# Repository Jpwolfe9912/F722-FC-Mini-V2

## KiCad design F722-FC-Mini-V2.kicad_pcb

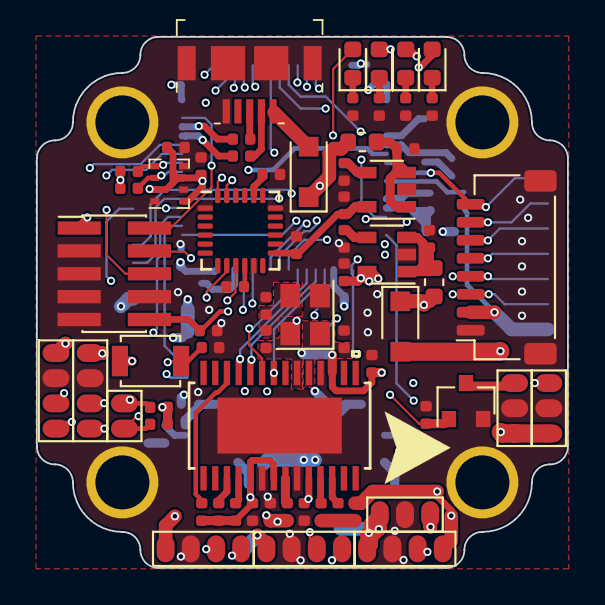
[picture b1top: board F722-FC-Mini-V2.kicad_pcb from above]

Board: 6 copper layers, 29.5 x 29.5 mm, 112 parts (0 on the bottom side), 91 nets.

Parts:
C1, C13, C17: 1uF; C_0402_1005Metric
C2, C14, C18: 10nF; C_0402_1005Metric
C3: 4.7uF; C_0402_1005Metric
C4, C5, C6, C7, C8, C9, C10, C15, C21, C22, C24, C25, C27, C31, C33, C45, C47: 0.1uF; C_0402_1005Metric
C11, C16, C19, C46: 2.2uF; C_0402_1005Metric
C12, C20: 10uF; C_0402_1005Metric
C23, C26: 22uF; C_0603_1608Metric
C28, C29: 10pF; C_0402_1005Metric
C30, C32: 4.7uF; C_0603_1608Metric
C34, C35: 820pF; C_0402_1005Metric
D1, D2, D4, D6: 90V, 2A; D_SOD-123F
D3: RED; LED_0603_1608Metric
D5: BLUE; LED_0603_1608Metric
D7: YELLOW; LED_0603_1608Metric
D9: GREEN; LED_0603_1608Metric
FB1, FB3: 100 @ 100 Mhz; L_0603_1608Metric
FB2: 100 @ 100 MHz; L_0603_1608Metric
H1, H2, H3, H4: MountingHole_Pad; MountingHole_3mm_M2_20x20
J1, J4, J6: Conn_01x03; Conn_3Pin
J2, J3, J7, J11, J13: Conn_01x04; Conn_4Pin
J5: Conn_01x06; JST_SH_SM06B-SRSS-TB_1x06-1MP_P1.00mm_Horizontal
J9: Conn_01x08; JST_SH_SM08B-SRSS-TB_1x08-1MP_P1.00mm_Horizontal
J10: Conn_01x08; Conn_FC_Solder_8
J12: Conn_01x02; Conn_2Pin
J14: UJ2-MIBH-4-SMT-TR; USB_Micro_B_Female_UJ2-MIBH-G-SMT-TR
J16: Conn_02x05_Odd_Even; PinHeader_2x05_P1.27mm_Vertical_SMD
L1, L2: 15uH; L_Bourns-SRN3015
L5: Arrow
Q1: BSS138; SOT-23
R1, R9, R10, R12, R21, R23, R31: 1k; R_0402_1005Metric
R2, R18, R27: 10k; R_0402_1005Metric
R3, R4: 3.7k; R_0402_1005Metric
R5, R8: 4.7k; R_0402_1005Metric
R6: 330; R_0402_1005Metric
R7, R15: 22; R_0402_1005Metric
R11, R20: 20k; R_0402_1005Metric
R13, R22: 3.8k; R_0402_1005Metric
R14, R16: 75; R_0402_1005Metric
R17: 589; R_0402_1005Metric
R19, R25: 200k; R_0402_1005Metric
R24, R28: 56k; R_0402_1005Metric
R26: 100; R_0402_1005Metric
SW1: SW_Push; SW_SPST_B3U-1000P
U1, U3: LP2985-3.3; SOT-23-5
U2: STM32F722RETx; LQFP-64_10x10mm_P0.5mm
U4: BMP280; Bosch_LGA-8_2x2.5mm_P0.65mm_ClockwisePinNumbering
U5, U8: MP4462; DFN-10-1EP_3x3mm_P0.5mm_EP1.7x2.5mm
U6: MAX7456EUI+; MAX7456EUI&plus_T
U7: MPU-6000; InvenSense_QFN-24_4x4mm_P0.5mm
U10: W25Q128JVS; SOIC-8_5.23x5.23mm_P1.27mm
Y1: 27MHz; Oscillator_SMD_Abracon_ASE-4Pin_3.2x2.5mm
Y2: CSTNE8M00G55Z000R0; OSC_CSTNE8M00G55Z000R0

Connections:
+3.3VA: C13.1, C14.1, FB2.1, U2.13
+3V3: C3.1, C4.1, C5.1, C6.1, C8.1, C9.1, C10.1, C16.1, C24.1, C25.1, C27.1, D3.2, FB2.2, J16.1, R1.1, R3.1, R4.1, R5.2, R8.2, R10.1, R12.1, SW1.1, U1.5, U2.1, U2.19, U2.32, U2.48, U2.64, U4.2, U4.6, U4.8, U6.3, U6.19, U6.21, U6.24, U10.3, U10.7, U10.8
+3V3_GYRO: C19.1, C45.1, U3.5, U7.13
+4V5: D1.1, D2.1, FB1.2, FB3.2, J3.1
+5V: C23.1, D1.2, D7.2, J1.1, J2.1, J6.1, J7.1, J13.1, L2.2, R11.1
+5V_USB: D2.2, J14.1
+9V: C26.1, J4.1, J5.1, J11.1, L1.2, R20.1
/Barometer/I2C3_SCL: R5.1, U2.41, U4.4
/Barometer/I2C3_SDA: R8.1, U2.40, U4.3
/CAM: C22.1, J4.3, R16.2
/Connectors/BUZ-: J1.3, Q1.3
/Connectors/CURR: J9.8, J10.1, U2.8
/Connectors/I2C1_SCL: J12.2, R4.2, U2.58
/Connectors/I2C1_SDA: J12.1, R3.2, U2.59
/Connectors/LED: J6.3, U2.15
/Connectors/M1: J9.3, J10.6, U2.26
/Connectors/M2: J9.4, J10.5, U2.25
/Connectors/M3: J9.5, J10.4, U2.57
/Connectors/M4: J9.6, J10.3, U2.56
/Connectors/NRST: C15.1, J16.10, U2.7
/Connectors/SWCLK: J16.4, U2.49
/Connectors/SWDIO: J16.2, U2.46
/Connectors/SWO: J16.6, U2.55
/Connectors/USB_D+: J14.3, R15.1
/Connectors/USB_D-: J14.2, R7.1
/Flash/SPI2_CS: U2.33, U10.1
/Flash/SPI2_MISO: U2.35, U10.2
/Flash/SPI2_MOSI: U2.36, U10.5
/Flash/SPI2_SCK: U2.34, U10.6
/Gyro/SPI3_CS: U2.50, U7.8
/Gyro/SPI3_MISO: U2.52, U7.9
/Gyro/SPI3_MOSI: U2.53, U7.24
/Gyro/SPI3_SCK: U2.51, U7.23
/MCU/ADC_VSENS: R27.1, R31.2, U2.10
/MCU/BOOT0: R2.1, SW1.2, U2.60
/MCU/BUZ-_MCU: Q1.1, R18.1, U2.24
/MCU/D+: R15.2, U2.45
/MCU/D-: R7.2, U2.44
/MCU/HSE_IN: U2.5, Y2.1
/MCU/HSE_OUT: R6.1, U2.6
/MCU/LED_BLUE: D5.2, U2.14
/MCU/SPI1_CS: U2.20, U6.8
/MCU/SPI1_MISO: U2.22, U6.11
/MCU/SPI1_MOSI: U2.23, U6.9
/MCU/SPI1_SCK: U2.21, U6.10
/MCU/UART1_RX: J3.3, U2.43
/MCU/UART1_TX: J3.4, U2.42
/MCU/UART2_RX: J7.3, J9.7, J10.2, U2.17
/MCU/UART2_TX: J7.4, U2.16
/MCU/UART3_RX: J2.3, J5.6, U2.29
/MCU/UART3_TX: J2.4, U2.28
/MCU/UART6_RX: J5.4, J13.3, U2.38
/MCU/UART6_TX: J5.3, J11.3, J13.4, U2.37
/OSD/CLKIN: C28.2, U6.5, Y1.1
/OSD/SAG: C20.2, U6.25
/OSD/XFB: R17.1, U6.6
/VID: J11.4, R14.1
GND: C1.2, C2.2, C3.2, C4.2, C5.2, C6.2, C8.2, C9.2, C10.2, C11.2, C15.2, C16.2, C17.2, C18.2, C19.2, C23.2, C24.2, C25.2, C26.2, C27.2, C28.1, C29.1, C30.1, C31.1, C32.1, C33.1, C45.2, C46.2, C47.2, D4.2, D6.2, H1.1, H2.1, H3.1, H4.1, J1.2, J2.2, J3.2, J4.2, J5.2, J5.5, J6.2, J7.2, J9.1, J10.8, J11.2, J13.2, J14.5, J14.SH, J16.3, J16.5, J16.7, J16.8, J16.9, Q1.2, R2.2, R9.2, R13.2, R16.1, R18.2, R19.2, R21.2, R22.2, R23.2, R24.2, R25.2, R26.2, R28.2, R31.1, U1.2, U2.18, U2.31, U2.47, U2.63, U3.2, U4.1, U4.5, U4.7, U5.6, U6.4, U6.20, U6.23, U6.29, U7.1, U7.11, U7.18, U8.6, U10.4, Y1.2, Y1.4, Y2.2
GNDA: C13.2, C14.2, U2.12
unnamed: C1.1, FB1.1, U1.1, U1.3
unnamed: C2.1, U1.4
unnamed: C7.1, U8.10
unnamed: C7.2, D4.1, L1.1, U8.1, U8.2
unnamed: C11.1, U2.30
unnamed: C12.1, C20.1, R14.2
unnamed: C12.2, U6.26
unnamed: C17.1, FB3.1, U3.1, U3.3
unnamed: C18.1, U3.4
unnamed: C21.1, U5.10
unnamed: C21.2, D6.1, L2.1, U5.1, U5.2
unnamed: C22.2, U6.22
unnamed: C29.2, R17.2, Y1.3
unnamed: C34.1, U5.4
unnamed: C34.2, R24.1
unnamed: C35.1, U8.4
unnamed: C35.2, R28.1
unnamed: C46.1, U7.20
unnamed: C47.1, U7.10
unnamed: D3.1, R21.1
unnamed: D5.1, R23.1
unnamed: D7.1, R26.1
unnamed: D9.1, R9.1
unnamed: R1.2, U6.18
unnamed: R6.2, Y2.3
unnamed: R10.2, U6.17
unnamed: R11.2, R13.1, U5.5
unnamed: R12.2, U6.12
unnamed: R19.1, U5.7
unnamed: R20.2, R22.1, U8.5
unnamed: R25.1, U8.7
VCC: C30.2, C31.2, C32.2, C33.2, D9.2, J9.2, J10.7, R27.2, U5.8, U5.9, U8.8, U8.9

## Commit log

2021-10-15 New files

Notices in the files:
parts and their libraries:
Copyright 2016 Accelerated Designs. All rights reserved.
